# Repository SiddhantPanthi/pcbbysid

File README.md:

# Description:

This is a simple PCB that you can use as a keychain in the shape of a character of a cartoon and it's eyes light up when it's dark with the help of a photoresistor hooked up with an NPN transistor.

# Parts list:

Battery x1 Push Switch x1 LED x2 Resistor x3 NPN-transistor x1 Photoresistor x1

# Some Glimpses

# Slack ID

osmiumxib07

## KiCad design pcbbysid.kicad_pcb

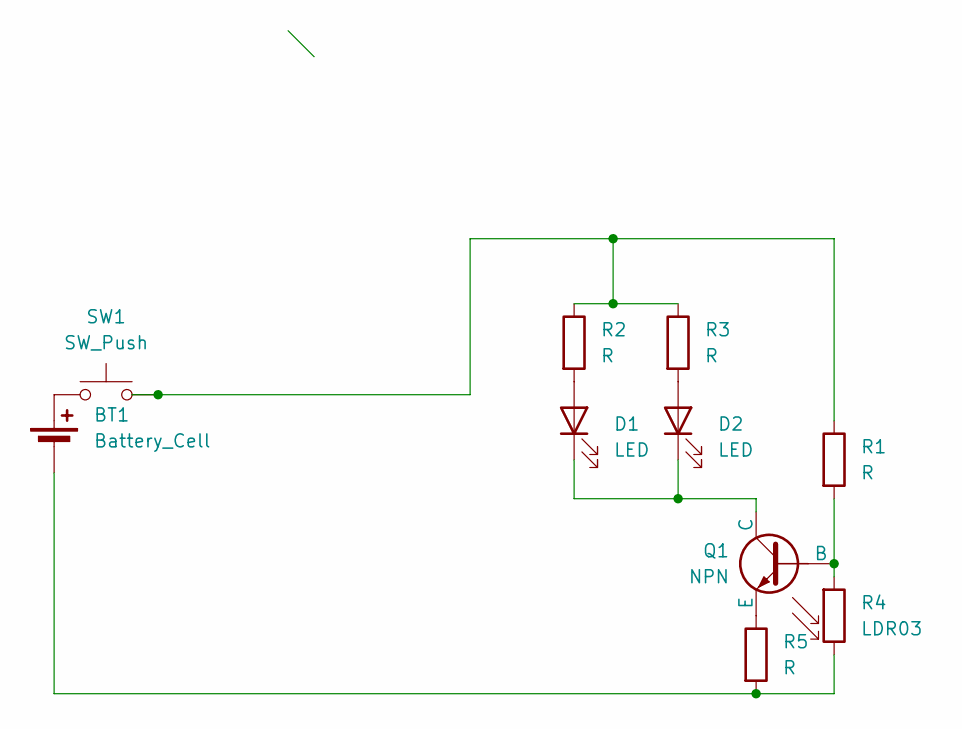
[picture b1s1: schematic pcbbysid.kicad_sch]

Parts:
BT1: Battery_Cell; BatteryHolder_Keystone_3034_1x20mm
D1, D2: LED; LED_D5.0mm
Q1: NPN; TO-92L_HandSolder
R1, R2, R3, R5: R; R_Axial_DIN0207_L6.3mm_D2.5mm_P7.62mm_Horizontal
R4: LDR03; R_LDR_5.1x4.3mm_P3.4mm_Vertical
SW1: SW_Push; SW_PUSH_6mm

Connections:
unnamed: BT1.1 (+), SW1.1
unnamed: BT1.2 (-), R4.2, R5.2
unnamed: D1.2 (A), R2.2
unnamed: D1.1 (K), D2.1 (K), Q1.1 (C)
unnamed: D2.2 (A), R3.2
unnamed: Q1.2 (B), R1.2, R4.1
unnamed: Q1.3 (E), R5.1
unnamed: R1.1, R2.1, R3.1, SW1.2

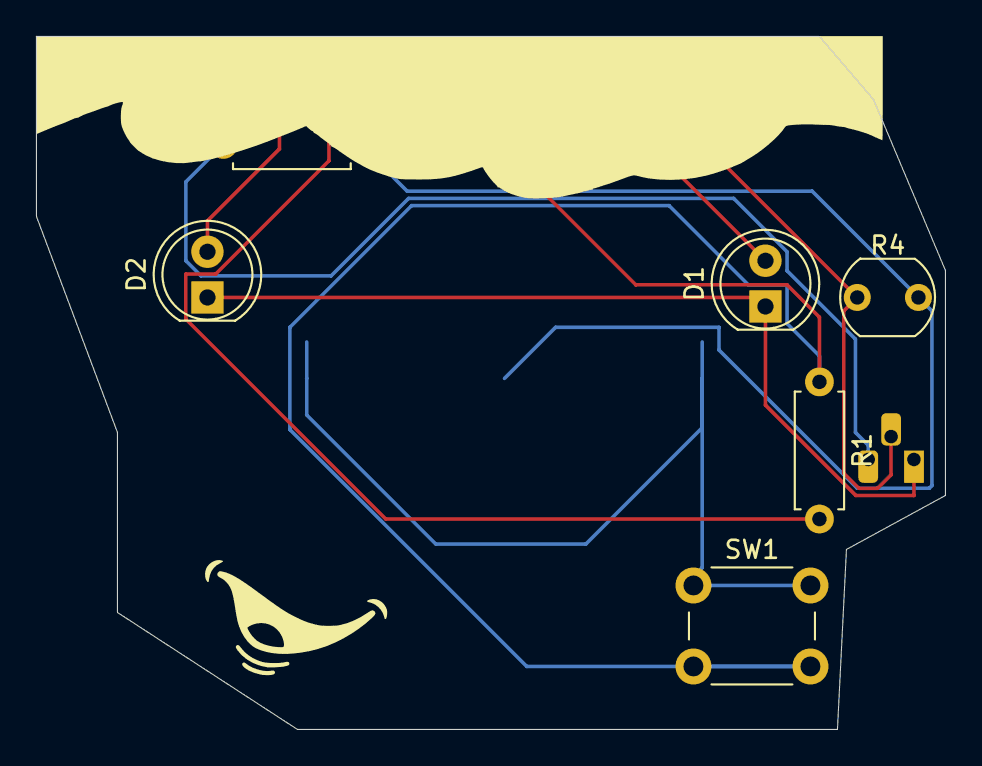
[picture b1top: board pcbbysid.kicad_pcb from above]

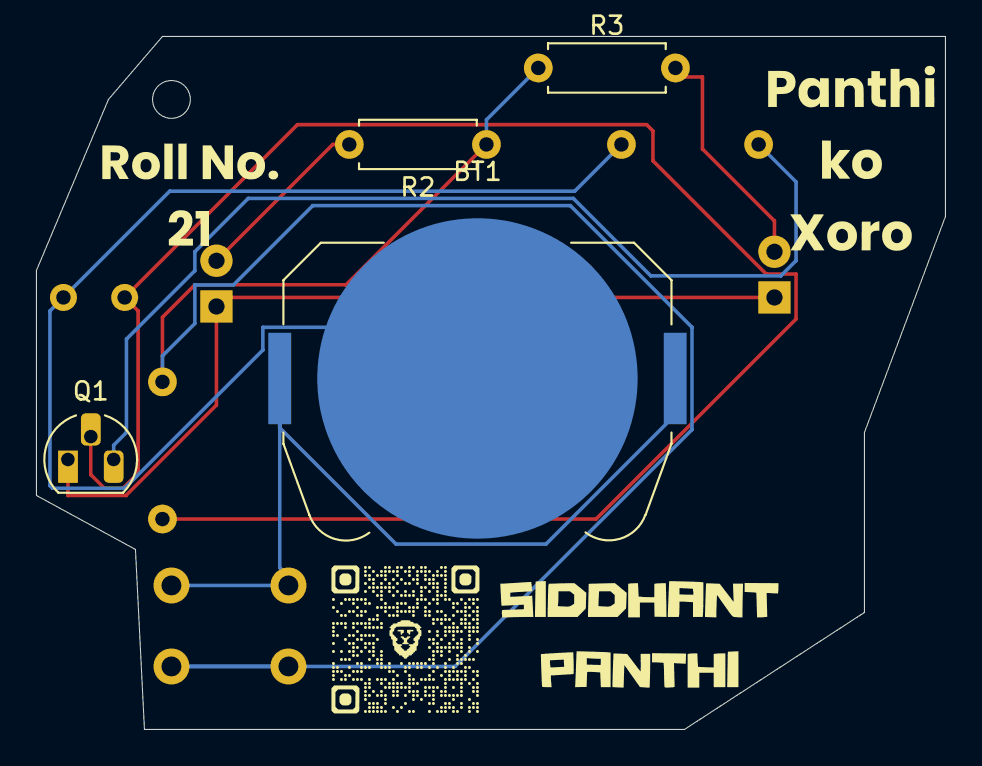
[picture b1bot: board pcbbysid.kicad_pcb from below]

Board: 2 copper layers, 50.5 x 38.5 mm, 10 parts (4 on the bottom side), 8 nets.

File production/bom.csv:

Designator,Footprint,Quantity,Value,LCSC Part #
BT1,BatteryHolder_Keystone_3034_1x20mm,1,Battery_Cell,
"D1, D2",LED_D5.0mm,2,LED,
Q1,TO-92L_HandSolder,1,NPN,
"R1, R2, R3, R5",R_Axial_DIN0207_L6.3mm_D2.5mm_P7.62mm_Horizontal,4,R,
R4,R_LDR_5.1x4.3mm_P3.4mm_Vertical,1,LDR03,
SW1,SW_PUSH_6mm,1,SW_Push,
